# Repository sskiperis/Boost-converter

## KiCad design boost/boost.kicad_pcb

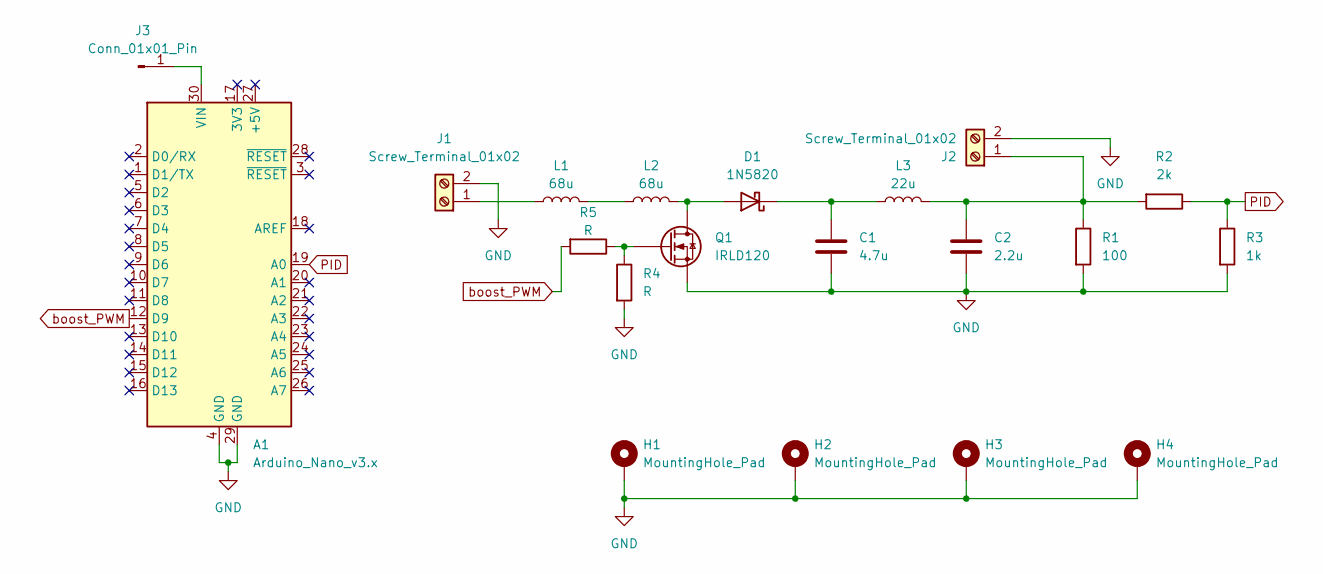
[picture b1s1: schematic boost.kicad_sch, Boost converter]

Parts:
A1: Arduino_Nano_v3.x; Arduino_Nano
C1: 4.7u; CP_Radial_D5.0mm_P2.50mm
C2: 2.2u; CP_Radial_D5.0mm_P2.50mm
D1: 1N5820; D_DO-201AD_P15.24mm_Horizontal
H1, H2, H3, H4: MountingHole_Pad; MountingHole_3.2mm_M3_Pad_TopBottom
J1, J2: Screw_Terminal_01x02; TerminalBlock_4Ucon_1x02_P3.50mm_Horizontal
J3: Conn_01x01_Pin; PinHeader_1x01_P1.00mm_Vertical
L1, L2: 68u; L_Radial_D7.5mm_P3.50mm_Fastron_07P
L3: 22u; L_Radial_D7.5mm_P3.50mm_Fastron_07P
Q1: IRLD120; DIP-4_W7.62mm_DualDrain
R1: 100; R_Axial_Power_L38.0mm_W9.0mm_P40.64mm
R2: 2k; R_Axial_DIN0207_L6.3mm_D2.5mm_P7.62mm_Horizontal
R3: 1k; R_Axial_DIN0207_L6.3mm_D2.5mm_P7.62mm_Horizontal
R4, R5: R; R_Axial_DIN0207_L6.3mm_D2.5mm_P7.62mm_Horizontal

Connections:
GND: A1.4 (GND), A1.29 (GND), C1.2, C2.2, H1.1, H2.1, H3.1, H4.1, J1.2, J2.2, Q1.2 (S), R1.2, R3.2, R4.2
unnamed: A1.30 (VIN), J3.1
unnamed: D1.2 (A), L2.2, Q1.1 (D)
unnamed: C1.1, D1.1 (K), L3.1
unnamed: J1.1, L1.1
unnamed: C2.1, J2.1, L3.2, R1.1, R2.2
unnamed: L1.2, L2.1
unnamed: Q1.3 (G), R4.1, R5.1
PID: A1.19 (A0), R2.1, R3.1
boost_PWM: A1.12 (D9), R5.2

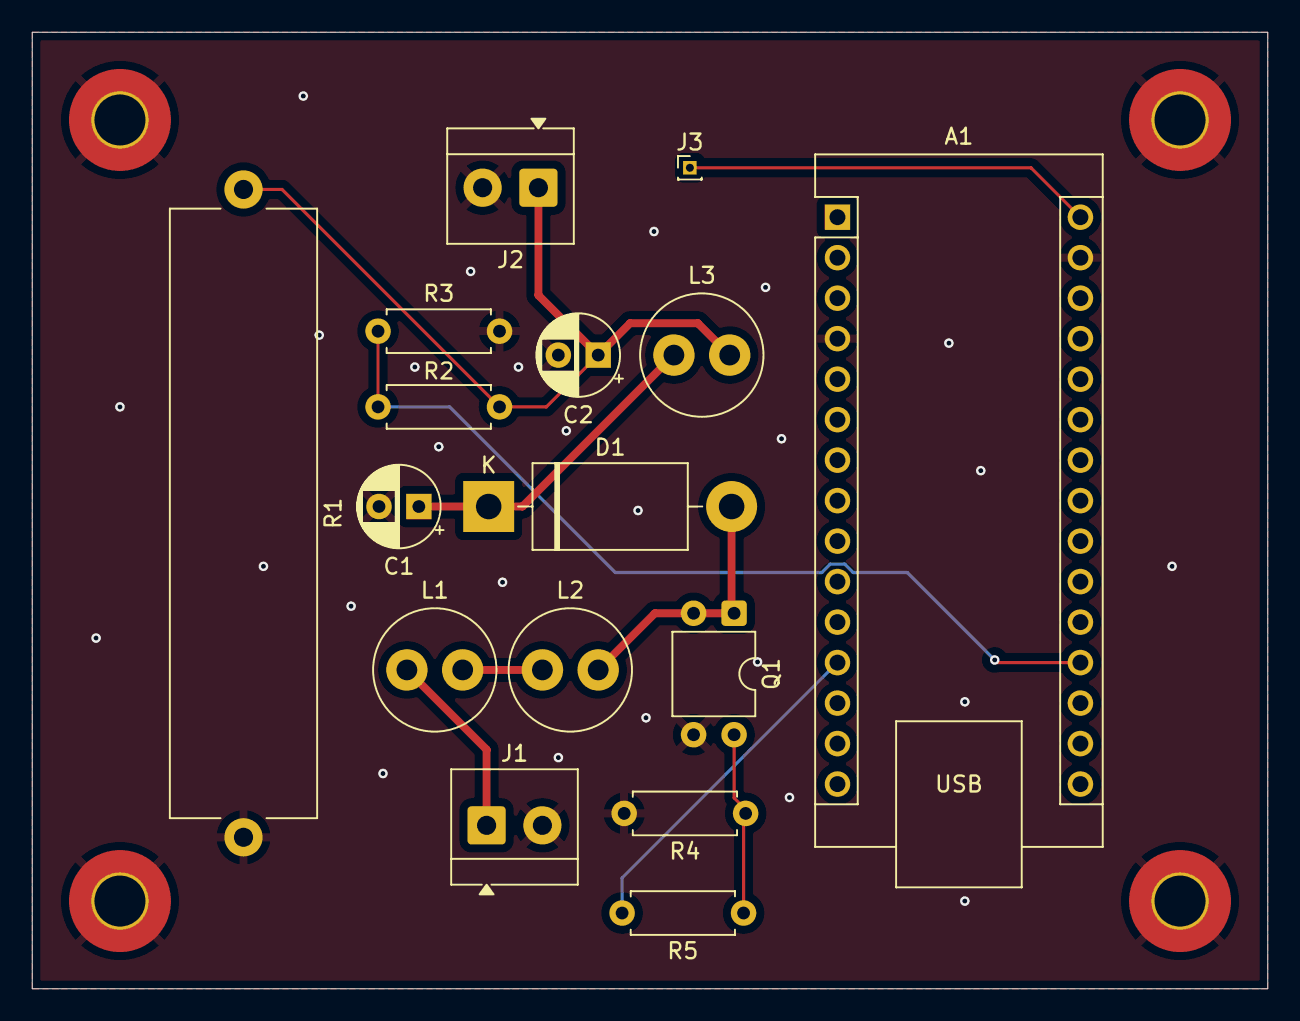
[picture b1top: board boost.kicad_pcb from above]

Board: 2 copper layers, 77.5 x 60.0 mm, 20 parts (0 on the bottom side), 10 nets.
